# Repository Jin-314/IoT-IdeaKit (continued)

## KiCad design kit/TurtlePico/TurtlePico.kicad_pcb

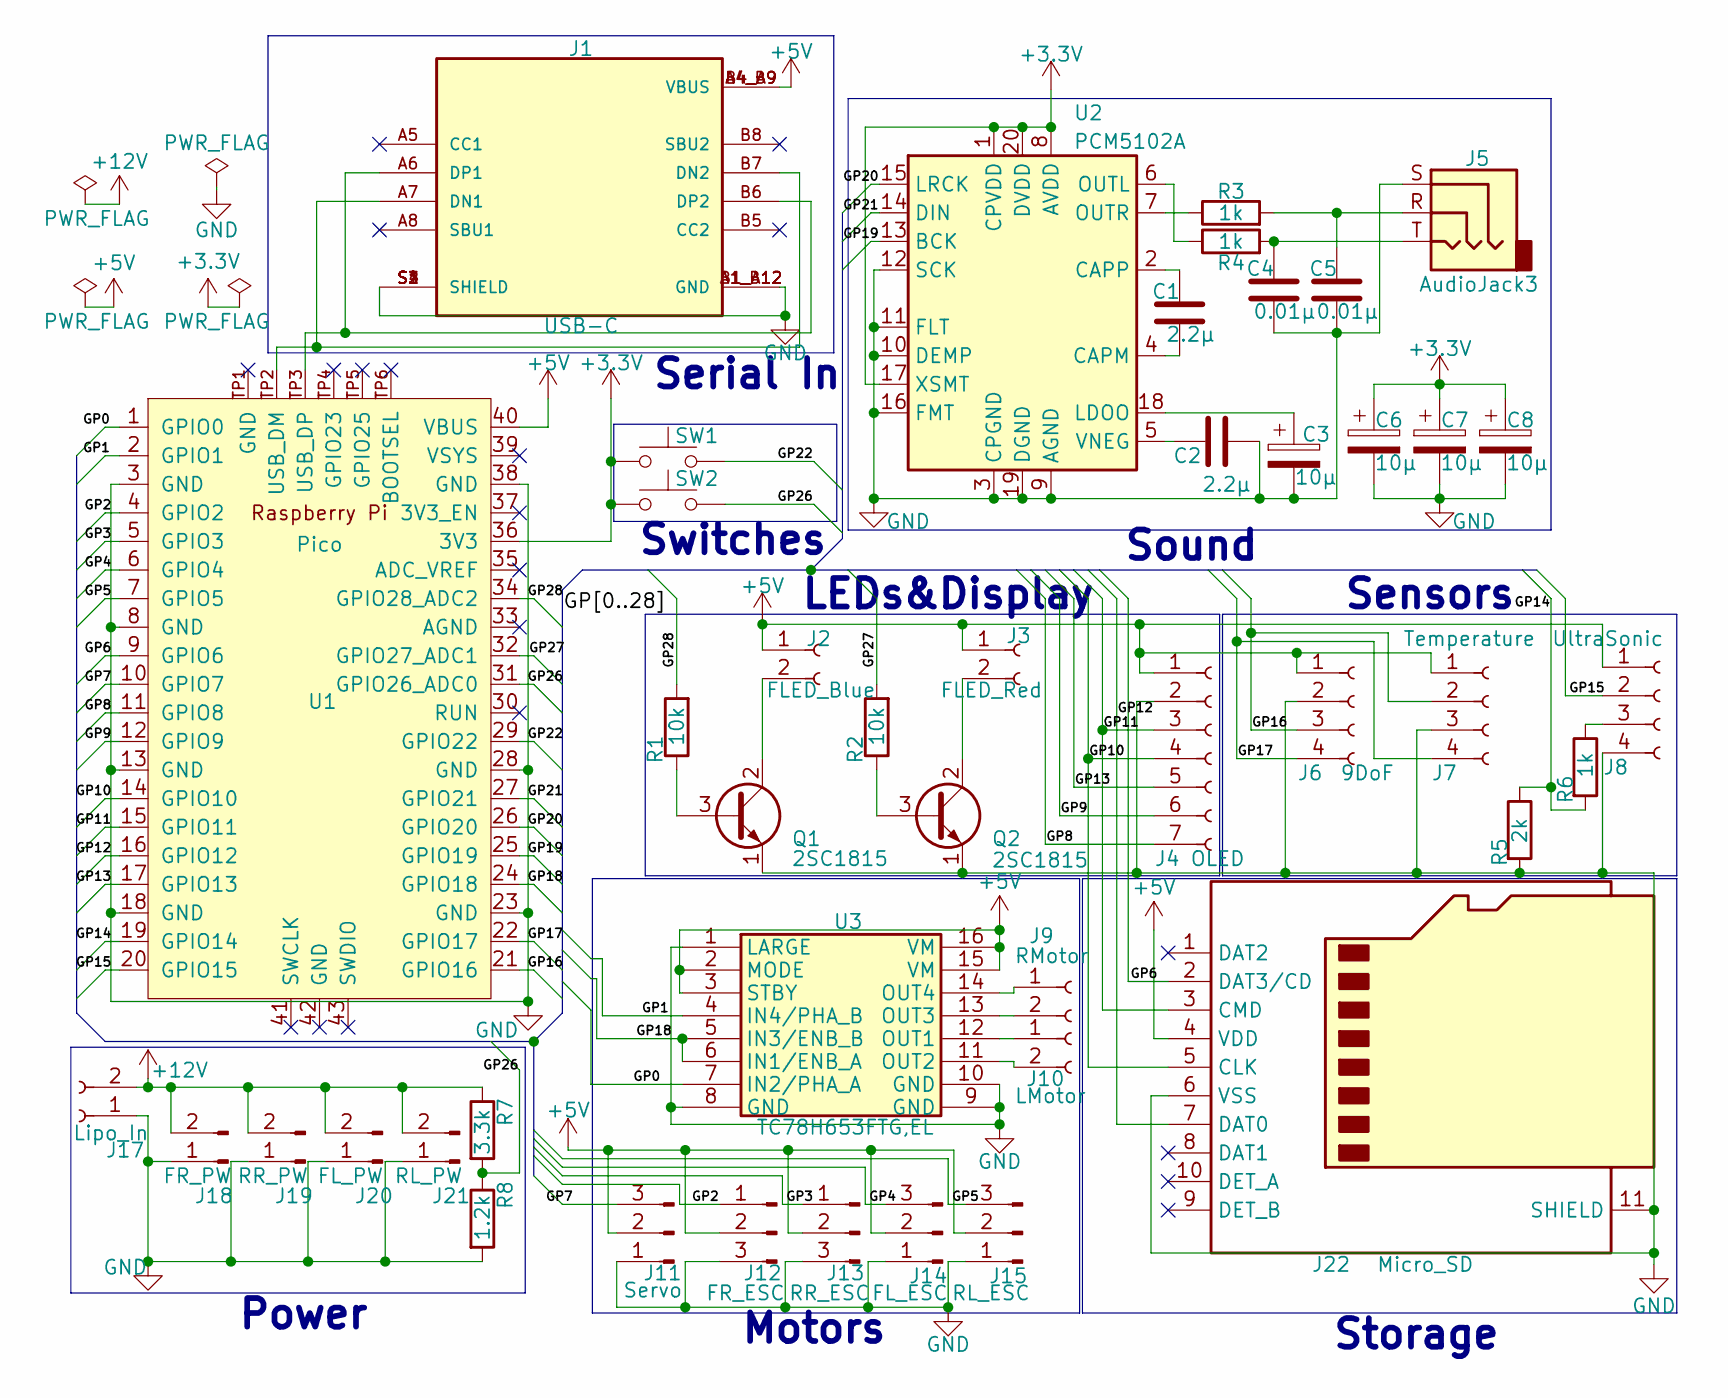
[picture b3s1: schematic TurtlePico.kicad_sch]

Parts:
C1, C2: 2.2µ; C_Disc_D5.1mm_W3.2mm_P5.00mm
C3, C6, C7, C8: 10µ; CP_Radial_D5.0mm_P2.00mm
C4, C5: 0.01µ; C_Disc_D4.3mm_W1.9mm_P5.00mm
J1: USB-C; NELTRON_5077CR-16SMC2-BK-TR; PARTREV B
J2: FLED_Blue; PinSocket_1x02_P2.54mm_Vertical
J3: FLED_Red; PinSocket_1x02_P2.54mm_Vertical
J4: OLED; JST_XH_S7B-XH-A_1x07_P2.50mm_Horizontal
J5: AudioJack3; Jack_3.5mm_Switronic_ST-005-G_horizontal
J6: 9DoF; JST_ZH_B4B-ZR_1x04_P1.50mm_Vertical
J7: Temperature; PinSocket_1x04_P2.54mm_Vertical
J8: UltraSonic; PinSocket_1x04_P2.54mm_Vertical
J9: RMotor; PinSocket_1x02_P2.54mm_Vertical
J10: LMotor; PinSocket_1x02_P2.54mm_Vertical
J11: Servo; PinHeader_1x03_P2.54mm_Horizontal
J12: FR_ESC; PinHeader_1x03_P2.54mm_Horizontal
J13: RR_ESC; PinHeader_1x03_P2.54mm_Horizontal
J14: FL_ESC; PinHeader_1x03_P2.54mm_Horizontal
J15: RL_ESC; PinHeader_1x03_P2.54mm_Horizontal
J17: Lipo_In; AMASS_XT60PW-M_1x02_P7.20mm_Horizontal
J18: FR_PW; AMASS_XT60PW-F_1x02_P7.20mm_Horizontal
J19: RR_PW; AMASS_XT60PW-F_1x02_P7.20mm_Horizontal
J20: FL_PW; AMASS_XT60PW-F_1x02_P7.20mm_Horizontal
J21: RL_PW; AMASS_XT60PW-F_1x02_P7.20mm_Horizontal
J22: Micro_SD; microSD_HC_Hirose_DM3AT-SF-PEJM5
Q1, Q2: 2SC1815; TO-92_Inline
R1, R2: 10k; R_Axial_DIN0207_L6.3mm_D2.5mm_P10.16mm_Horizontal
R3, R4, R6: 1k; R_Axial_DIN0207_L6.3mm_D2.5mm_P10.16mm_Horizontal
R5: 2k; R_Axial_DIN0207_L6.3mm_D2.5mm_P10.16mm_Horizontal
R7: 3.3k; R_Axial_DIN0207_L6.3mm_D2.5mm_P10.16mm_Horizontal
R8: 1.2k; R_Axial_DIN0207_L6.3mm_D2.5mm_P10.16mm_Horizontal
SW1, SW2: SW_Push; SW_SKRPACE010
U1: Pico; RPi_Pico_SMD_TH
U2: PCM5102A; PCM5102A_DIP
U3: TC78H653FTG,EL; DIP-16_W7.62mm; Mouser Part Number 757-TC78H653FTGEL

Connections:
+3.3V: C6.1, C7.1, C8.1, SW1.1, SW2.1, U1.36 (3V3), U2.1 (CPVDD), U2.8 (AVDD), U2.17 (XSMT), U2.20 (DVDD)
+5V: J1.A4_B9 (VBUS), J1.B4_A9 (VBUS), J2.1, J3.1, J4.1, J6.1, J7.1, J8.1, J11.2, J12.2, J13.2, J14.2, J15.2, J22.4 (VDD), U1.40 (VBUS), U3.2 (MODE), U3.3 (STBY), U3.15 (VM), U3.16 (VM)
+12V: J17.2, J18.2, J19.2, J20.2, J21.2, R7.1
/GP0: U1.1 (GPIO0), U3.7 (IN2/PHA_A)
/GP1: U1.2 (GPIO1), U3.4 (IN4/PHA_B)
/GP2: J12.1, U1.4 (GPIO2)
/GP3: J13.1, U1.5 (GPIO3)
/GP4: J14.3, U1.6 (GPIO4)
/GP5: J15.3, U1.7 (GPIO5)
/GP6: J22.2 (DAT3/CD), U1.9 (GPIO6)
/GP7: J11.3, U1.10 (GPIO7)
/GP8: J4.7, U1.11 (GPIO8)
/GP9: J4.6, U1.12 (GPIO9)
/GP10: J4.4, J22.5 (CLK), U1.14 (GPIO10)
/GP11: J4.3, J22.3 (CMD), U1.15 (GPIO11)
/GP12: J22.7 (DAT0), U1.16 (GPIO12)
/GP13: J4.5, U1.17 (GPIO13)
/GP14: R5.1, R6.2, U1.19 (GPIO14)
/GP15: J8.2, U1.20 (GPIO15)
/GP16: J6.3, J7.2, U1.21 (GPIO16)
/GP17: J6.4, J7.4, U1.22 (GPIO17)
/GP18: U1.24 (GPIO18), U3.5 (IN3/ENB_B), U3.6 (IN1/ENB_A)
/GP19: U1.25 (GPIO19), U2.13 (BCK)
/GP20: U1.26 (GPIO20), U2.15 (LRCK)
/GP21: U1.27 (GPIO21), U2.14 (DIN)
/GP22: SW1.2, U1.29 (GPIO22)
/GP26: R7.2, R8.1, SW2.2, U1.31 (GPIO26_ADC0)
/GP28: R1.2, U1.34 (GPIO28_ADC2)
unnamed: C4.1, J5.T, R4.2
unnamed: C5.1, J5.R, R3.2
unnamed: J1.A7 (DN1), J1.B7 (DN2), U1.TP2 (USB_DM)
unnamed: J1.A6 (DP1), J1.B6 (DP2), U1.TP3 (USB_DP)
unnamed: J2.2, Q1.2 (C)
unnamed: J3.2, Q2.2 (C)
unnamed: J8.3, R6.1
unnamed: J9.1, U3.14 (OUT4)
unnamed: J9.2, U3.13 (OUT3)
unnamed: J10.1, U3.12 (OUT1)
unnamed: J10.2, U3.11 (OUT2)
unnamed: Q1.3 (B), R1.1
unnamed: Q2.3 (B), R2.1
unnamed: C1.2, U2.4 (CAPM)
unnamed: C1.1, U2.2 (CAPP)
unnamed: C3.1, U2.18 (LDOO)
unnamed: R4.1, U2.6 (OUTL)
unnamed: R3.1, U2.7 (OUTR)
unnamed: C2.1, U2.5 (VNEG)

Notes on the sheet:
Sensors
LEDs&Display
Serial In
Switches
Motors
Sound
Storage
Power

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
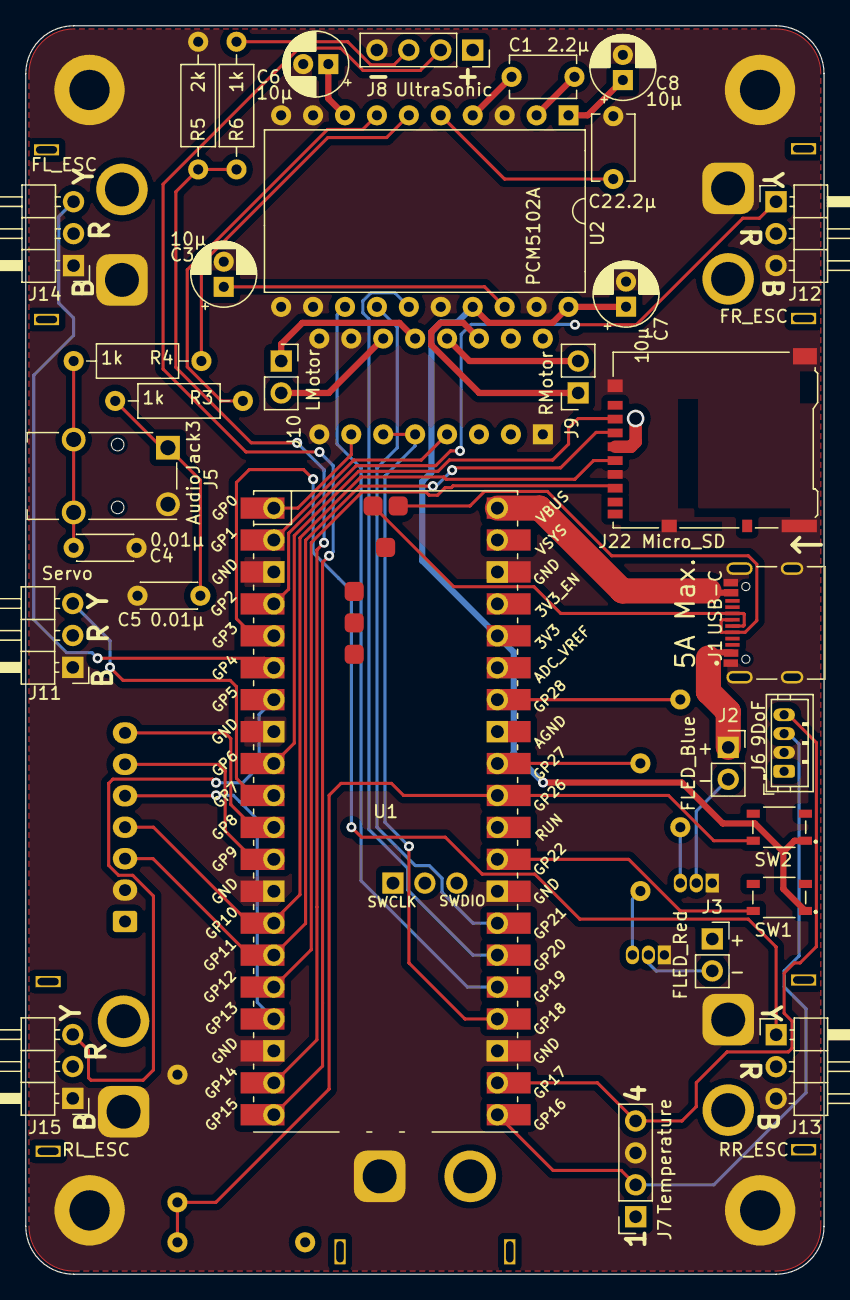
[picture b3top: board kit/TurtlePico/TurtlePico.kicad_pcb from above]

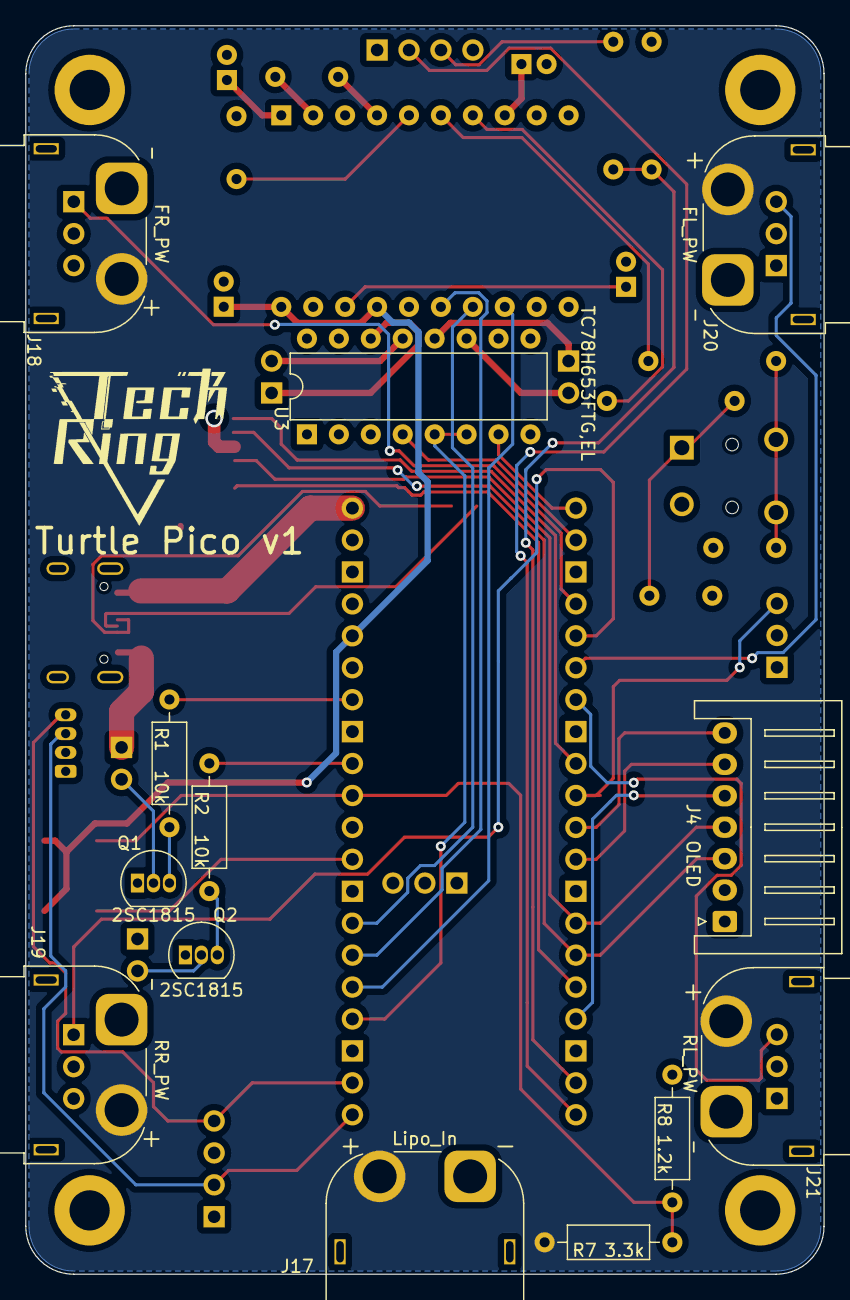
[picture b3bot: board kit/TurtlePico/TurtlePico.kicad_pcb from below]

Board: 4 copper layers, 63.5 x 99.3 mm, 44 parts (13 on the bottom side), 49 nets.

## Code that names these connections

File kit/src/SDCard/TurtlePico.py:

# Turtle Pico Pin Define File

LED_R           = 18
LED_L           = 4

SW_R            = 22
SW_L            = 3

MOTOR_EN        = 14
MOTOR_R         = 17
MOTOR_L         = 15

SPI_ID		= 1
SPI_SCK         = 10
SPI_MOSI        = 11
SPI_MISO        = 12

OLED_CS         = 7
OLED_DC         = 6
OLED_RST        = 5

SD_CS           = 27

I2C_ID		= 0
I2C_SCL         = 9
I2C_SDA         = 8

I2S_ID		= 0
I2S_BCLK        = 19
I2S_LRCLK       = 20
I2S_SDATA       = 21

ESC_SERVO_FR    = 28
ESC_SERVO_RR    = 16
ESC_SERVO_FL    = 2
ESC_SERVO_RL    = 13

TRIG_TX         = 1
ECHO_RX         = 0

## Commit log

2023-07-29 add ultrasonic sensor
2023-07-29 add oled and more
2023-07-29 add Temperature sensor
2023-07-29 add sensors_web & oled code
2023-07-29 edit
2023-08-01 add sch and library
2023-08-01 edit ignore
2023-08-01 edit gitignore
2023-08-01 move
2023-08-01 edit pico library
2023-08-01 add TypeC Lib and more
2023-08-02 add Servo and DC Motor
2023-08-03 change
2023-08-03 fix sch
2023-08-03 add BLDC and fix sch
2023-08-05 add Turtle Pico that is Driver
2023-08-05 add pic
2023-08-07 add step and change 4layers
2023-08-15 add text
2023-08-23 edit connection
2023-09-12 add sdcard
2023-10-19 add MusicPlayer
2024-02-02 add version folder
2024-02-02 change version
2024-02-02 add gitattribute
2024-02-03 Turtle Pico Update v1.0
2024-02-03 add step file v1.0
2024-02-03 change BJT and some design
2024-03-19 add smarthome project
2024-03-19 rm cached
2024-04-23 add Ironman Program
2024-04-25 add ledtape
2024-04-25 ironman programm add timeout
2024-05-06 update v1.1 fix usb
2024-05-07 update v.1 change uart and ultrasonic pin
2024-05-07 Create LICENSE
2024-05-09 add TurtlePico.py that is Pin Define
2024-05-12 edit TurtlePico.py
2024-07-15 add case
2024-07-17 add bom and change some directory
2024-07-17 remove cache
2024-07-17 add document
2024-07-17 change directory structure
2024-07-17 change ignore file
2024-07-17 case
2024-07-17 change LICENSE
2024-07-17 add route License file
2024-07-17 update uppercase
2024-07-17 Turtle Pico Overview
2024-07-29 add Turtle Dashboard
2024-07-30 add clock function(only digital) in TurtlePico-Dashboard
2024-07-30 add clock function(analog) in TurtlePico-Dashboard
2024-07-31 add menu class and format the coding
2024-08-30 add pos file
2024-09-10 add mini model
2024-09-10 update minimal model
2024-09-10 update schematics
2024-09-16 update PCB and edit schematic
2024-11-08 add Weather to Dashboard
